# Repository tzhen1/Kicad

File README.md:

# Kicad
Various electronic hardware projects on Kicad. 

Projects include:
DC/DC Converter
TSAL LED

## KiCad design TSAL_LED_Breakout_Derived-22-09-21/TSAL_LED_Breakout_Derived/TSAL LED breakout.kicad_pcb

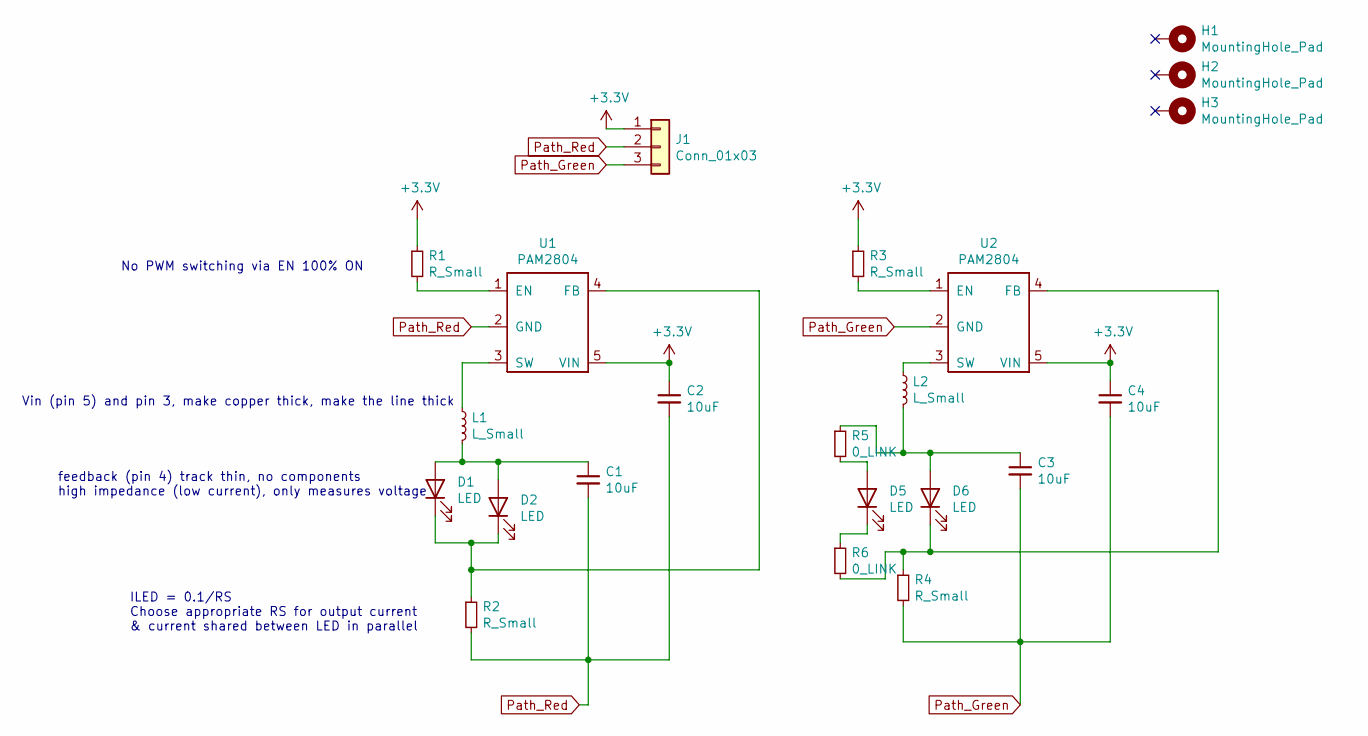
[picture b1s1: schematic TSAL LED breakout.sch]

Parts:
C1, C2, C3, C4: 10uF; C_0805_2012Metric
D1, D2, D5, D6: LED; LED_KT DDLM31.13
H1, H2, H3: MountingHole_Pad; MountingHole_3.2mm_M3_Pad_Via
J1: Conn_01x03; Molex_KK-254_AE-6410-03A_1x03_P2.54mm_Vertical
L1, L2: L_Small; L_1812_4532Metric
R1, R2, R3, R4: R_Small; R_0805_2012Metric
R5, R6: 0_LINK; R_1210_3225Metric
U1, U2: PAM2804

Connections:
+3V3: C2.1, C4.1, J1.1, R1.1, R3.1, U1.5 (VIN), U2.5 (VIN)
unnamed: C1.1, D1.2 (A), D2.2 (A), L1.2
unnamed: C3.1, D6.2 (A), L2.2, R5.1
unnamed: D1.1 (K), D2.1 (K), R2.1, U1.4 (FB)
unnamed: D5.1 (K), R6.1
unnamed: D5.2 (A), R5.2
unnamed: D6.1 (K), R4.1, R6.2, U2.4 (FB)
unnamed: L1.1, U1.3 (SW)
unnamed: L2.1, U2.3 (SW)
unnamed: R1.2, U1.1 (EN)
unnamed: R3.2, U2.1 (EN)
Path_Green: C3.2, C4.2, J1.3, R4.2, U2.2 (GND)
Path_Red: C1.2, C2.2, J1.2, R2.2, U1.2 (GND)

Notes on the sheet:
No PWM switching via EN 100% ON
ILED = 0.1/RS Choose appropriate RS for output current & current shared between LED in parallel
Vin (pin 5) and pin 3, make copper thick, make the line thick
feedback (pin 4) track thin, no components high impedance (low current), only measures voltage

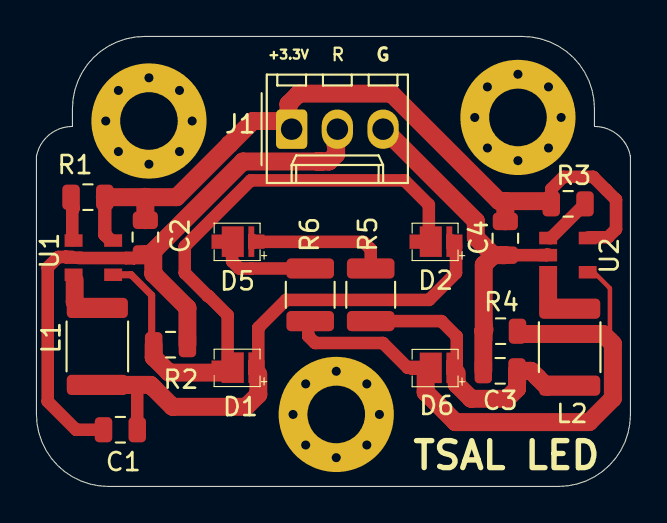
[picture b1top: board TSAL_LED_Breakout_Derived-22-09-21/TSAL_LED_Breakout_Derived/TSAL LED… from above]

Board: 2 copper layers, 33.0 x 25.0 mm, 22 parts (0 on the bottom side), 13 nets.

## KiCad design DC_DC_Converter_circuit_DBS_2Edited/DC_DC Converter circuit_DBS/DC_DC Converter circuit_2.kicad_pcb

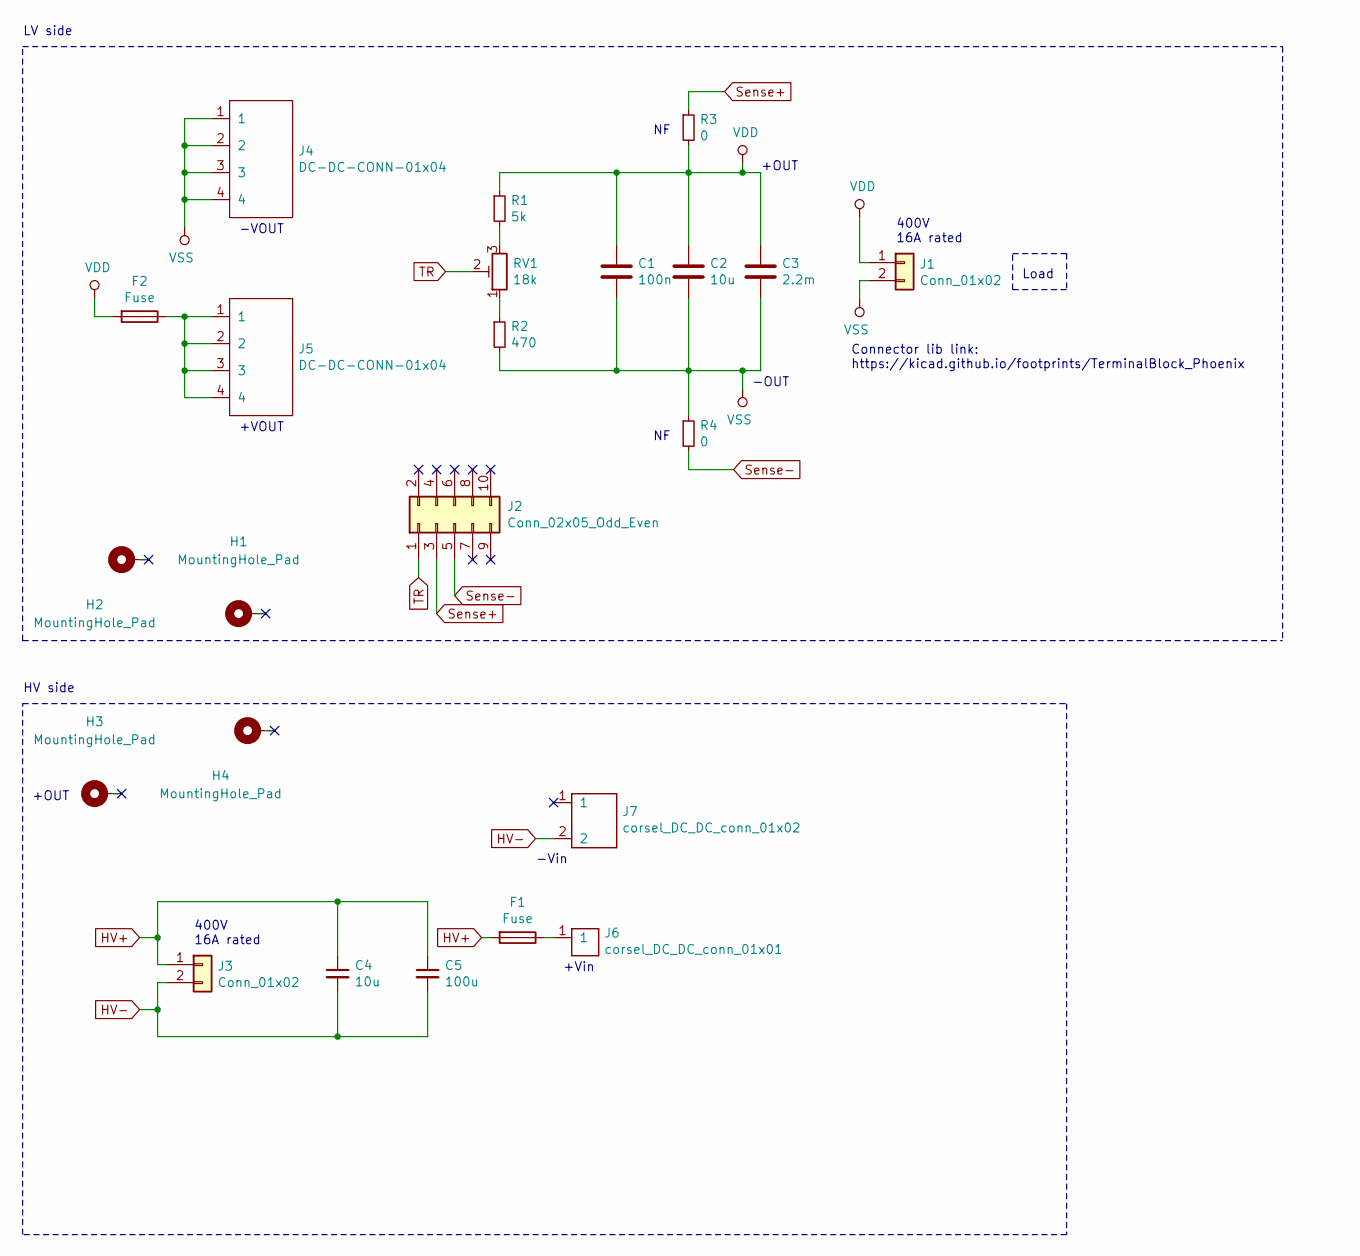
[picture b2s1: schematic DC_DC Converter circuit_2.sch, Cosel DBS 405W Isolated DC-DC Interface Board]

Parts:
C1: 100n; C_1210_3225Metric_Pad1.33x2.70mm_HandSolder
C2: 10u; C_1210_3225Metric_Pad1.33x2.70mm_HandSolder
C3: 2.2m; CP_Radial_D10.0mm_P5.00mm
C4: 10u; CP_Radial_D10.0mm_P5.00mm
C5: 100u; CP_Radial_D18.0mm_P7.50mm
F1: Fuse; Fuseholder_Cylinder-6.3x32mm_Schurter_0031-8002_Horizontal_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
F2: Fuse; Fuseholder_Cylinder-5x20mm_Schurter_0031_8201_Horizontal_Op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
H1, H2, H3, H4: MountingHole_Pad; MountingHole_5.3mm_M5_Pad_Via
J1, J3: Conn_01x02; TerminalBlock_Phoenix_MKDS-3-2-5.08_1x02_P5.08mm_Horizontal
J2: Conn_02x05_Odd_Even; PinHeader_2x05_P2.54mm_Vertical
J4, J5: DC-DC-CONN-01x04; Corsel_DC_DC_01x04
J6: corsel_DC_DC_conn_01x01; cosel_DC_DC_-01x01
J7: corsel_DC_DC_conn_01x02; corsel_DC_DC_01x02
R1: 5k; R_Axial_DIN0207_L6.3mm_D2.5mm_P10.16mm_Horizontal
R2: 470; R_Axial_DIN0207_L6.3mm_D2.5mm_P10.16mm_Horizontal
R3, R4: 0; R_0805_2012Metric
RV1: 18k; Potentiometer_Bourns_3296W_Vertical

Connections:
HV+: C4.1, C5.1, F1.2, J3.1
HV-: C4.2, C5.2, J3.2, J7.2
unnamed: F1.1, J6.1
unnamed: F2.1, J5.1, J5.2, J5.3, J5.4
unnamed: R1.2, RV1.3
unnamed: R2.1, RV1.1
Sense+: J2.3, R3.1
Sense-: J2.5, R4.2
TR: J2.1, RV1.2
VDD: C1.1, C2.1, C3.1, F2.2, J1.1, R1.1, R3.2
VSS: C1.2, C2.2, C3.2, J1.2, J4.1, J4.2, J4.3, J4.4, R2.2, R4.1

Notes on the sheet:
+OUT
-OUT
Load
LV side
HV side
Connector lib link: https://kicad.github.io/footprints/TerminalBlock_Phoenix
400V 16A rated
-VOUT
+VOUT
-Vin
+Vin

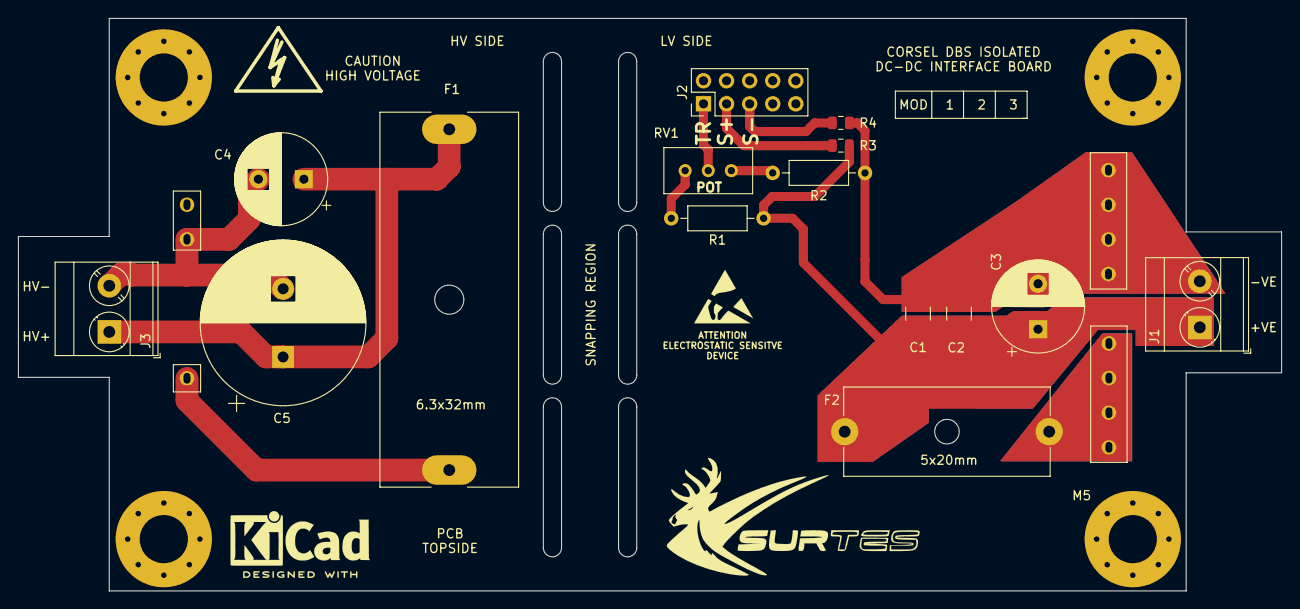
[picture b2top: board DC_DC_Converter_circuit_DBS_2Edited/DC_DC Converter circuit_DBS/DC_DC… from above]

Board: 2 copper layers, 139.0 x 63.0 mm, 23 parts (0 on the bottom side), 11 nets.

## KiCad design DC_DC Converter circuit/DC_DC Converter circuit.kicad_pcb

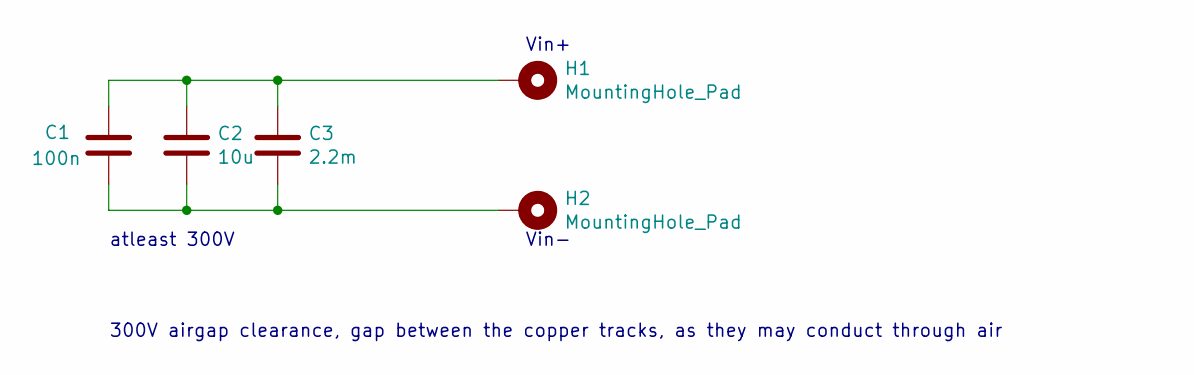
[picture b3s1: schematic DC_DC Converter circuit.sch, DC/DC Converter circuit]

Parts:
C1: 100n; C_1210_3225Metric_Pad1.33x2.70mm_HandSolder
C2: 10u; C_1210_3225Metric_Pad1.33x2.70mm_HandSolder
C3: 2.2m; CP_Radial_D18.0mm_P7.50mm
H1, H2: MountingHole_Pad; MountingHole_2.5mm_Pad_Via

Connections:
unnamed: C1.1, C2.1, C3.1, H1.1
unnamed: C1.2, C2.2, C3.2, H2.1

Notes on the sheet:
Vin+
Vin-
atleast 300V
300V airgap clearance, gap between the copper tracks, as they may conduct through air

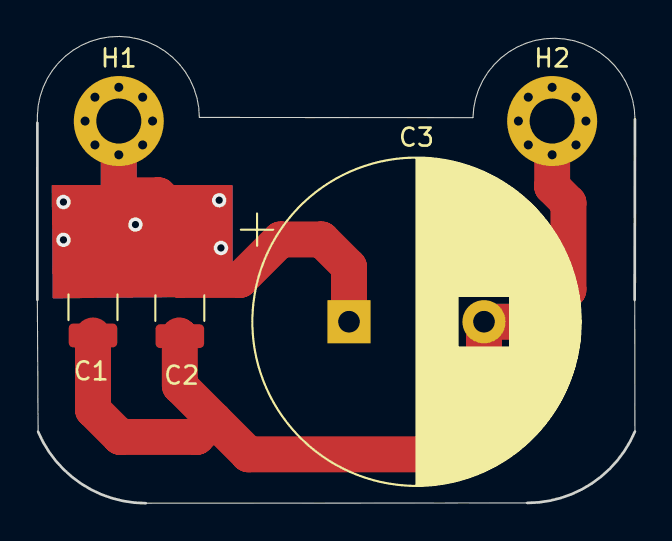
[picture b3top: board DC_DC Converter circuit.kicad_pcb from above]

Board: 2 copper layers, 33.2 x 25.9 mm, 5 parts (0 on the bottom side), 2 nets.

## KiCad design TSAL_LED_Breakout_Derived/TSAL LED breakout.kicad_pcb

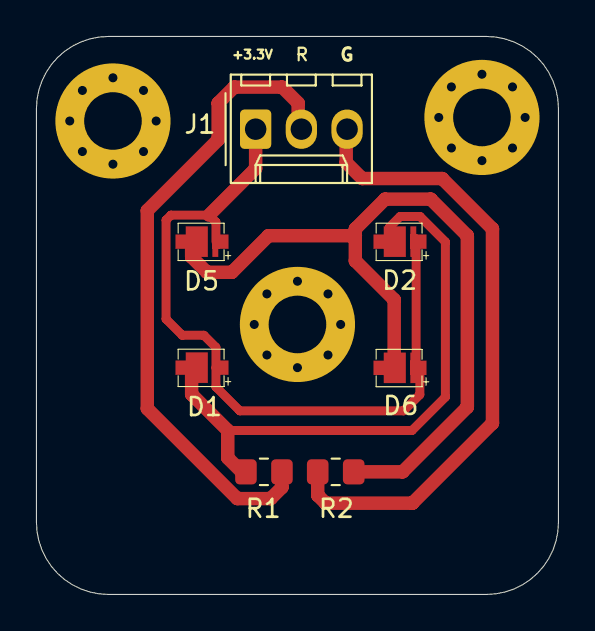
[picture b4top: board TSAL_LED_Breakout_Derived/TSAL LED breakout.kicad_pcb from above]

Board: 2 copper layers, 29.0 x 31.0 mm, 10 parts (0 on the bottom side), 5 nets.

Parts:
D1, D2, D5, D6: LED; LED_KT DDLM31.13
H1, H2, H3: MountingHole_Pad; MountingHole_3.2mm_M3_Pad_Via
J1: Conn_01x03; Molex_KK-254_AE-6410-03A_1x03_P2.54mm_Vertical
R1, R2: 22; R_0805_2012Metric_Pad1.20x1.40mm_HandSolder

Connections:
+3V3: D1.2, D2.2, D5.2, D6.2, J1.1
unnamed: D1.1, D2.1, R1.2
unnamed: D5.1, D6.1, R2.2
Path_Green: J1.3, R2.1
Path_Red: J1.2, R1.1

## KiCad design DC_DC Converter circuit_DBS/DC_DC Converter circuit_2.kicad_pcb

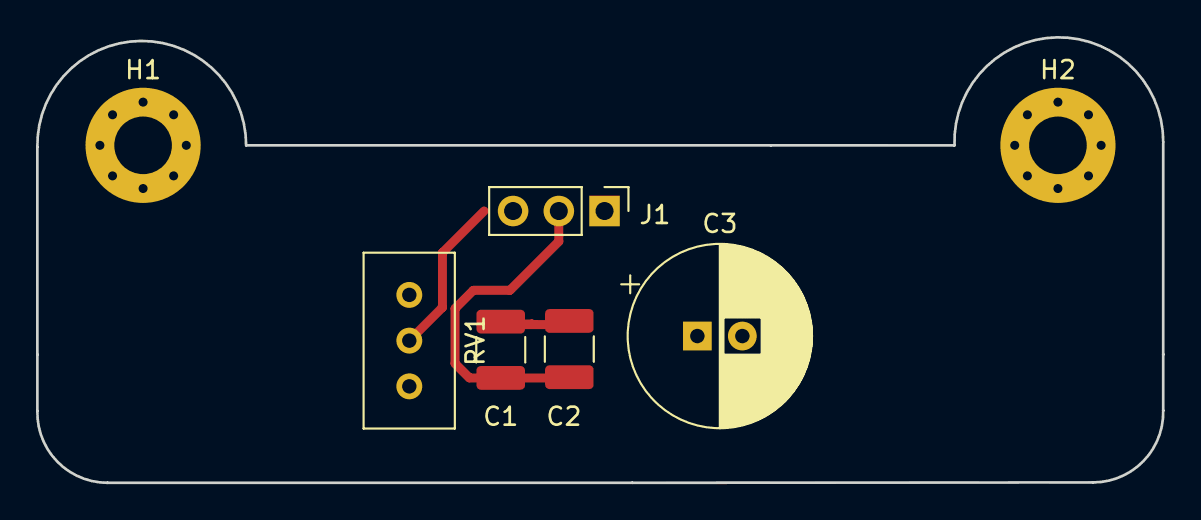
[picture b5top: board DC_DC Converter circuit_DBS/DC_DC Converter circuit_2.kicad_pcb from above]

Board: 2 copper layers, 62.5 x 24.7 mm, 7 parts (0 on the bottom side), 3 nets.

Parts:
C1: 100n; C_1210_3225Metric_Pad1.33x2.70mm_HandSolder
C2: 10u; C_1210_3225Metric_Pad1.33x2.70mm_HandSolder
C3: 2.2m; CP_Radial_D10.0mm_P2.50mm
H1, H2: MountingHole_Pad; MountingHole_3.2mm_M3_Pad_Via
J1: Conn_01x03_Female; PinHeader_1x03_P2.54mm_Vertical
RV1: R_POT_TRIM; Potentiometer_Bourns_3296W_Vertical

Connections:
Sense+: C1.1, C2.1, C3.1, H1.1, J1.2
Sense-: C1.2, C2.2, C3.2, H2.1, J1.1, RV1.1
TR: J1.3, RV1.2

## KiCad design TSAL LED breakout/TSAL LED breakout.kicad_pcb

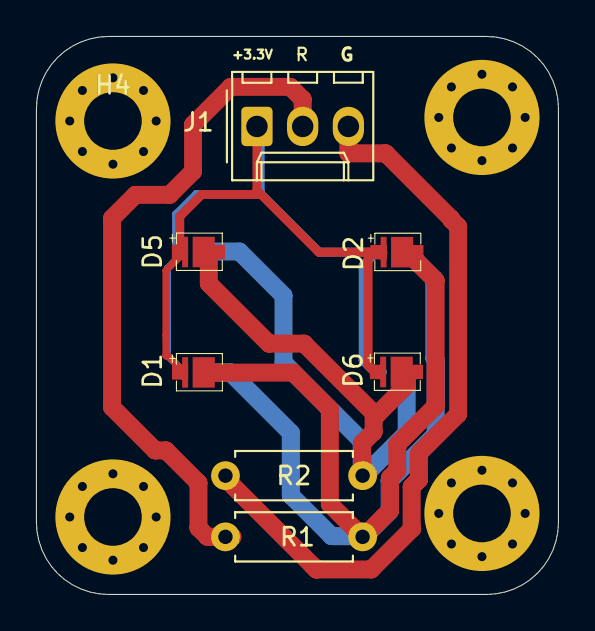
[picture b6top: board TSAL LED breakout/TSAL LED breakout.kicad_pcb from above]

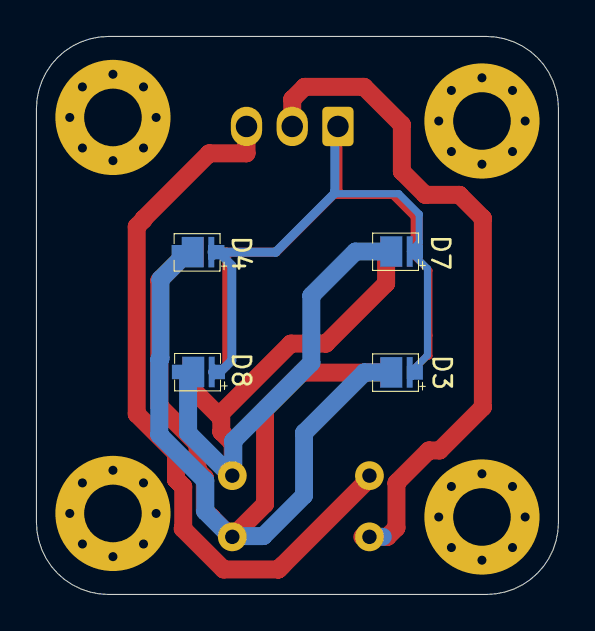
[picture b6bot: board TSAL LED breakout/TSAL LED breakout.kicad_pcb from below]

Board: 2 copper layers, 29.0 x 31.0 mm, 15 parts (4 on the bottom side), 5 nets.

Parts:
D1, D2, D3, D4, D5, D6, D7, D8: LED; LED_KT DDLM31.13
H1, H2, H3, H4: MountingHole_Pad; MountingHole_3.2mm_M3_Pad_Via
J1: Conn_01x03; Molex_KK-254_AE-6410-03A_1x03_P2.54mm_Vertical
R1, R2: 22; R_Axial_DIN0207_L6.3mm_D2.5mm_P7.62mm_Horizontal

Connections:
+3V3: D1.2, D2.2, D3.2, D4.2, D5.2, D6.2, D7.2, D8.2, J1.1
unnamed: D1.1, D2.1, D3.1, D4.1, R1.2
unnamed: D5.1, D6.1, D7.1, D8.1, R2.2
Path_Green: J1.3, R2.1
Path_Red: J1.2, R1.1

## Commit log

2021-10-11 fix: improved traces TSAL LED
